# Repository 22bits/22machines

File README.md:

# 22machines

  Sistema modular electromecánico de generación y activación sonora, derivado de Tutupá drum machine, y desarrollado en Chile por el [Colectivo 22bits](https://www.22bits.org) (Bárbara Molina y Matías Serrano). 
  
  Motivados por un pensamiento tecnofeminista, proponemos replantearnos la tecnología y su incidencia en los cuerpos. Esta plataforma busca promover el bricolaje electrónico en comunidades latinoamericanas, y se propone como una alternativa, desde nuestros materiales y componentes disponibles en esta parte del mundo, al formato Eurorack. Todos los módulos se comunican a través de pulsos de 5v, y son alimentados por fuentes DC de 9 a 12v. Si no entiendes de qué estamos hablando, ve al apartado de preguntas frecuentes al final de la página.
  
  Únete a nuestra comunidad de experimentación en [Facebook!](https://www.facebook.com/groups/442825269573096/) 

  ### [C01-SEQ](https://github.com/22bits/22machines/tree/master/C01-SEQ)

    Secuenciador de 4 pistas y 16 pasos

  ### [C02-BEAT](https://github.com/22bits/22machines/tree/master/C02-BEAT)

    Conversor de trigger a movimiento percusivo de servomotor para 4 pistas

  ### [C03-MULT](https://github.com/22bits/22machines/tree/master/C03-MULT)

    Multiplicador pasivo, permite copiar una señal en otras dos. Cada módulo incluye 4 mults

  ### [C04-LD12](https://github.com/22bits/22machines/tree/master/C04-LD)

    Convierte un pulso en una señal de 12V, de longitud variable. Permite utilizar cargas de 12V, como tiras LED.

  ### [C05-22mini](https://github.com/22bits/22machines/tree/master/C05-22mini) 

    Drum machine mecánica, controladora de servos de 2 pasos y 8 pistas.
    Utilizada en talleres de introducción al sistema 22machines.

_________________________

 ### [¿? Preguntas frecuentes](https://github.com/22bits/22machines/tree/master/FAQ)
 
 ____________________
<br /><span xmlns:dct="http://purl.org/dc/terms/" href="http://purl.org/dc/dcmitype/InteractiveResource" property="dct:title" rel="dct:type">22machines</span> por <a xmlns:cc="http://creativecommons.org/ns#" href="http://www.22bits.org" property="cc:attributionName" rel="cc:attributionURL">Bárbara Molina & Matías Serrano</a> se distribuye bajo una <a rel="license" href="http://creativecommons.org/licenses/by-nc-sa/4.0/">Licencia Creative Commons Atribución-NoComercial-CompartirIgual 4.0 Internacional</a>.

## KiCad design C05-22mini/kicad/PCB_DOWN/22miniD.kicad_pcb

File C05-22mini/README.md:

# C05-22mini
(tutumini)

##### Diseñada por Colectivo 22bits (http://22bits.org)
##### Bárbara Molina & Matías Serrano
##### Programada por Elías Zacarías (http://blog.damnsoft.org/)
___________________________________

22mini es una drum machine mecánica de 2 pistas y 8 pasos, donde cada relación entra paso y pista puede activar un servo motor en una acción percusiva.

(click en la imagen para ver video)

### Especificaciones (1a versión):

    - 2 pistas con salidas individuales
    - Hasta 8 pasos por pista
    - Salidas pueden ser para controlar servo motores o generar triggers de 5v
    - Control de tempo
    - Control de Play/Pause/Clear
    - 2 pantallas de visualización, 
    - Entrada y salida de Sync no dependientes 
    - Cada máquina puede seleccionar si obedece al pulso externo o al interno a través de un switch
    - Operación a través de 9~12V con centro positivo
    
### Descripción de funcionamiento
  
22mini está programada en Arduino, la cual lee la información ingresada a través de los botones, lo muestra en la pantalla de LEDS, y activa los servomotores según la secuencia. La velocidad de ésta es dependiente de la perilla de tempo o de la entrada de Sync, que avanza un paso a cada lectura de pulso en Sync IN.

Electrónicamente, todos los componentes están en función del Arduino. 8 de los 9 botones ingresan a través de un circuito integrado CD4021 (PISO; Parallel IN, Serial OUT), el cuál permite leer 8 entradas paralelas utilizando solo tres pines del Arduino. El noveno botón ingresa directamente a éste. Los botones de la columna izquiera permiten seleccionar qué pista quiero escribir, y los de la fila inferior en qué paso quiero activar la secuencia. El botón de OFFBEAT permite visualizar entre pasos impares (1, 3, 5 y 7) y pares (2, 4, 6, 8). MUTE, al mantenerse presionado, permite silenciar una pista o pasos, dejando la oportunidad de generar patrones de 1/8 hasta 8/8. El botón de Play permite pausar o reproducir la secuencia, y al mantenerse presionado limpia todas las secuencias.
    
Las luces LED son controladas a través de un circuito integrado MAX4219, el cuál está diseñado para manejar matrices LED de hasta 8x8. Está sobreestimado, ya que solo maneja 17 leds de 64 posibles. La razón será explicada más adelante, en la sección de modificaciones. 

El tempo es controlado por pulsos de 5v y 15ms. Cada vez que Arduino recibe uno de estos pulsos, entiende que debe avanzar un paso la secuencia. Este pulso puede provenir internamente, obedeciendo al potenciómetro de TEMPO, o de forma externa, obedeciendo a la entrada SYNC IN. Este permite sincronizar 22minis entre ellas, o con otros secuenciadores (como los Korg, por ejemplo). Cada 22mini copia en la salida Sync OUT el tempo al cuál está avanzando. El Switch SYNC EXT/INT permite que la secuencia avance según el tempo externo o interno a disposición, evitando que cada 22mini sea esclava de la entrada de sync, y pueda independizase de esta, generando nuevos ritmos complejos.

Las salidas están predeterminadas para controlar servomotores en un movimiento percusivo. Practicamente cualquier servomotor de 5v y 180º es posible de activar, siempre y cuando no supere 1A de consumo. Cada salida de servo es alimentada por un único regulador 7805, por lo que la limitación de amperaje depende de éste. 

La alimentación del circuito puede ser de 9 a 12V, con un amperaje de 1A para motores más pequeños (como el SG09)
    
### Modificaciones sugeridas
    
   - 22mini está programada exactamente con el mismo código que C01-SEQ, solo varía a través de la línea "#define _22_MINI". Si está comentada, asignará los botones y leds para la versión de 4 pistas y 16 pasos, lo cual puede generar problemas para una 22mini.
   
   - Si se comenta la línea "#define SERVO_OUTPUT", las salidas pasan a ser de triggers de 5V, lo que permitiría utilizar estas para activar otro tipo de actuadores, usarlos como sync para otros secuenciadores, etc. Además cada conector cuenta con 5v (hasta 1A) y un GND.
   
   - La pantalla puede ser re-programada para que cuente hasta 16 pasos, y así tener más posibilidades rítmicas. Se sugiere utilizar dos horizontales para este conteo. Esta modificación no ha sido programada aún.
   
   - Hay pads de la PCB que no incluyen componentes, los cuales están abiertos para agregar variaciones. Estos son 4 pines análogos (A4, A5, A6, A7), uno digital (D3), D10 y D11 para salidas no definidas en el código, TX y RX.  

### Sugerencias al ensamblar:
  
   - D23 y R19 reducen el voltaje de la entrada de SYNC, no deben soldarse.
   - El emisor de Q1 debe ir a GND, por lo que se debe puentear al disipador.
   - Los Condensadores electrolíticos deben ir horizontales para que no interfieran espacialmente con la placa superior. Pueden ir soldados hacia arriba o hacia abajo según criterio de la persona que lo ensamble.
   - Soldar los headers utilizando los separadores como guías, para hacer más sencillo el montaje y desmontaje de las dos placas

 _____________________________
 
C05 - 22mini por Bárbara Molina & Matías Serrano se distribuye bajo una Licencia Creative Commons Atribución-NoComercial-CompartirIgual 4.0 Internacional.
 
Colectivo 22bits promueve cualquier tipo de modificación y hackeo a la máquina, no así el uso comercial que se le pueda dar sin expresa autorización de sus creadores. Si te fabricas una, la utilizas en tu set, o la usas para algo nuevo, haznos saber y te compartiremos en nuestras redes sociales (si te interesa) :)

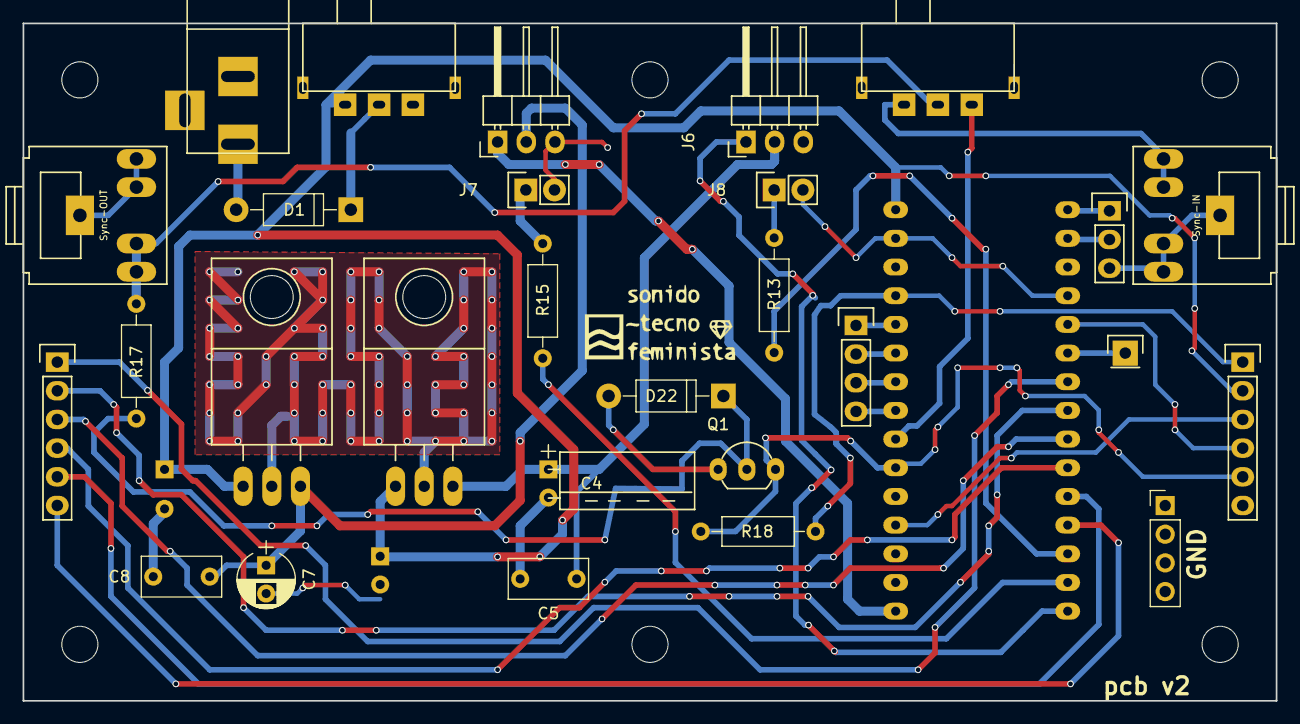
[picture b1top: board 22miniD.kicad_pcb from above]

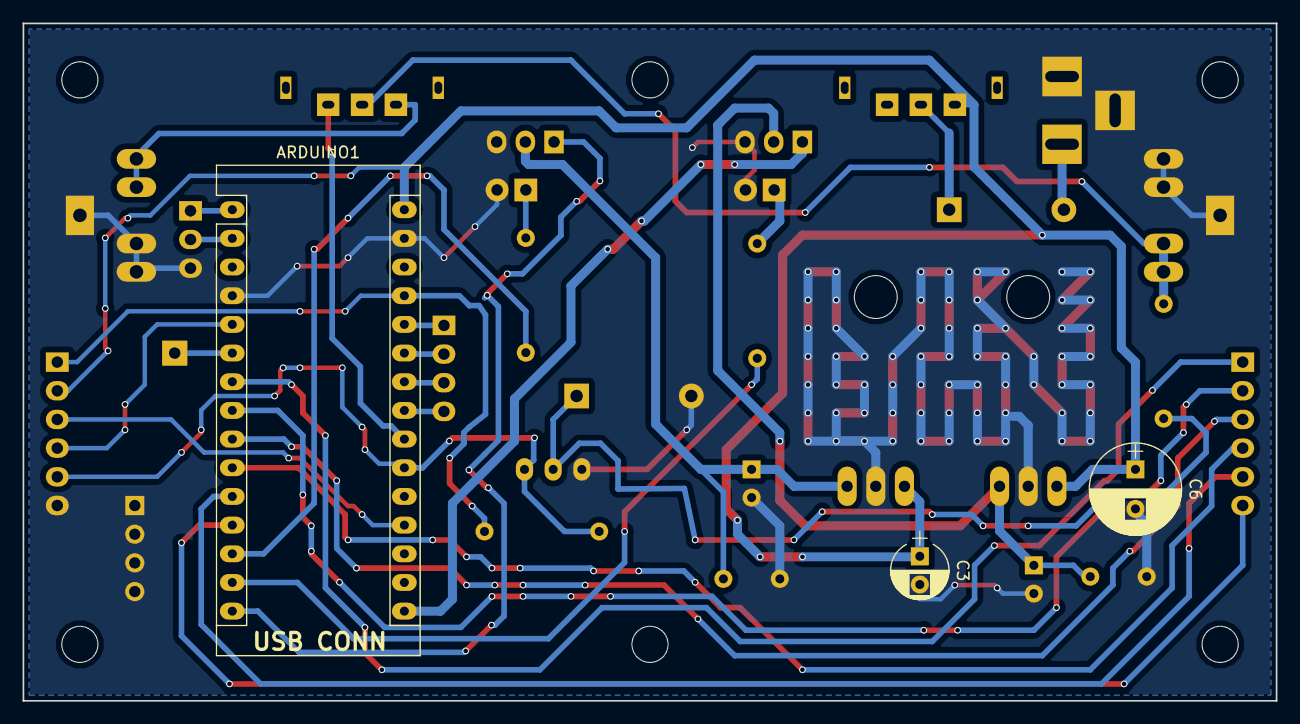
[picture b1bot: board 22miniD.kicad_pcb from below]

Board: 2 copper layers, 111.0 x 60.0 mm, 30 parts (3 on the bottom side), 33 nets.

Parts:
ARDUINO1: ARDUINO_NANO; Arduino_Nano
C3: 100u; CP_Radial_D5.0mm_P2.50mm
C4, C7: 10u; CP_Radial_D5.0mm_P2.50mm
C5, C8: 100n; C_Rect_L7.0mm_W3.5mm_P5.00mm
C6: 100u; CP_Radial_D8.0mm_P3.50mm
D1, D22: 1N4007; D_DO-41_SOD81_P10.16mm_Horizontal
J1: DC_IN; BARREL_JACK
J2: D3; Pin_Header_Straight_1x01
J3: TXRX; Pin_Header_Straight_1x03
J4: ANALOGS; Pin_Header_Straight_1x04
J5: SERVO1; Pin_Header_Angled_1x03
J6: SERVO2; Pin_Header_Angled_1x03
J7: OUT1; Pin_Header_Straight_1x02
J8: OUT2; Pin_Header_Straight_1x02
J9: Sync-IN; Tayda_3.5mm_stereo_TRS_jack_A-853
J10: Sync-OUT; Tayda_3.5mm_stereo_TRS_jack_A-853
J11: 4021/7219DOWN; Socket_Strip_Straight_1x06
J14: AUX BUS DOWN; Socket_Strip_Straight_1x06
Q1: PN2222A; TO-92_Inline_Wide
R13, R15: 100R; R_Axial_DIN0207_L6.3mm_D2.5mm_P10.16mm_Horizontal
R17: 1K; R_Axial_DIN0207_L6.3mm_D2.5mm_P10.16mm_Horizontal
R18: 10k; R_Axial_DIN0207_L6.3mm_D2.5mm_P10.16mm_Horizontal
SW4: ON/OFF; SW_SPDT_Lateral
SW11: SYNCSEL; SW_SPDT_Lateral
U3, U4: L7805; TO-220_Neutral123_Horizontal_LargePads

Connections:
+5V: ARDUINO1.27, J14.1, R18.2
+5VL: C4.1, C5.1, J6.2, U3.3
+5VP: C7.1, C8.1, J5.2, U4.3
+12V: ARDUINO1.30, C3.1, C6.1, J14.2, SW4.1, U3.1, U4.1
GND: ARDUINO1.4, ARDUINO1.29, C3.2, C4.2, C5.2, C6.2, C7.2, C8.2, D22.2, J1.2, J1.3, J3.3, J5.3, J6.3, J7.2, J8.2, J9.1, J9.2, J9.4, J10.1, J10.2, J10.4, J14.6, Q1.1, U3.2, U4.2
unnamed: ARDUINO1.1, J3.1
unnamed: ARDUINO1.2, J3.2
unnamed: ARDUINO1.5, J14.4
unnamed: ARDUINO1.6, J2.1
unnamed: ARDUINO1.7, J11.1
unnamed: ARDUINO1.8, J11.2
unnamed: ARDUINO1.9, J11.3
unnamed: ARDUINO1.10, J11.4
unnamed: ARDUINO1.11, J11.5
unnamed: ARDUINO1.12, J11.6
unnamed: ARDUINO1.13, R13.2
unnamed: ARDUINO1.14, R15.2
unnamed: ARDUINO1.15, J6.1
unnamed: ARDUINO1.16, J5.1
unnamed: ARDUINO1.19, J14.3
unnamed: ARDUINO1.21, J14.5, Q1.3, R18.1
unnamed: ARDUINO1.22, SW11.3
unnamed: ARDUINO1.23, J4.4
unnamed: ARDUINO1.24, J4.3
unnamed: ARDUINO1.25, J4.2
unnamed: ARDUINO1.26, J4.1
unnamed: D1.1, SW4.2
unnamed: D1.2, J1.1
unnamed: D22.1, Q1.2, R17.1
unnamed: J7.1, R15.1
unnamed: J8.1, R13.1
unnamed: J9.3, J9.5, SW11.1
unnamed: J10.3, J10.5, R17.2, SW11.2

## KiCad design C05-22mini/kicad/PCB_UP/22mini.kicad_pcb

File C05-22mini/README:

C05 - 22mini
(tutumini)
Diseñada por Colectivo 22bits (http://22bits.org)
Bárbara Molina & Matías Serrano
Programada por Elías Zacarías (http://blog.damnsoft.org/)

C05 - 22mini por Bárbara Molina & Matías Serrano se distribuye bajo una Licencia Creative Commons Atribución-NoComercial-CompartirIgual 4.0 Internacional.
___________________________________

22mini es una drum machine mecánica de 2 pistas y 8 pasos, donde cada relación entra paso y pista puede activar un servo motor en una acción percusiva.

  Especificaciones (1a versión):

    - 2 pistas con salidas individuales
    - Hasta 8 pasos por pista
    - Salidas pueden ser para controlar servo motores o generar triggers de 5v
    - Control de tempo
    - Control de Play/Pause/Clear
    - 2 pantallas de visualización, 
    - Entrada y salida de Sync no dependientes 
    - Cada máquina puede seleccionar si obedece al pulso externo o al interno a través de un switch
    - Operación a través de 9~12V con centro positivo
    
  Descripción de funcionamiento
  
    22mini está programada en Arduino, la cual lee la información ingresada a través de los botones, lo muestra en la pantalla de LEDS, y activa los servomotores según la secuencia. La velocidad de ésta es dependiente de la perilla de tempo o de la entrada de Sync, que avanza un paso a cada lectura de pulso en Sync IN.
    Electrónicamente, todos los componentes están en función del Arduino. 8 de los 9 botones ingresan a través de un circuito integrado CD4021 (PISO; Parallel IN, Serial OUT), el cuál permite leer 8 entradas paralelas utilizando solo tres pines del Arduino. El noveno botón ingresa directamente a éste. Los botones de la columna izquiera permiten seleccionar qué pista quiero escribir, y los de la fila inferior en qué paso quiero activar la secuencia. El botón de OFFBEAT permite visualizar entre pasos impares (1, 3, 5 y 7) y pares (2, 4, 6, 8). MUTE, al mantenerse presionado, permite silenciar una pista o pasos, dejando la oportunidad de generar patrones de 1/8 hasta 8/8. El botón de Play permite pausar o reproducir la secuencia, y al mantenerse presionado limpia todas las secuencias.
    Las luces LED son controladas a través de un circuito integrado MAX4219, el cuál está diseñado para manejar matrices LED de hasta 8x8. Está sobreestimado, ya que solo maneja 17 leds de 64 posibles. La razón será explicada más adelante, en la sección de modificaciones. 
    El tempo es controlado por pulsos de 5v y 15ms. Cada vez que Arduino recibe uno de estos pulsos, entiende que debe avanzar un paso la secuencia. Este pulso puede provenir internamente, obedeciendo al potenciómetro de TEMPO, o de forma externa, obedeciendo a la entrada SYNC IN. Este permite sincronizar 22minis entre ellas, o con otros secuenciadores (como los Korg, por ejemplo). Cada 22mini copia en la salida Sync OUT el tempo al cuál está avanzando. El Switch SYNC EXT/INT permite que la secuencia avance según el tempo externo o interno a disposición, evitando que cada 22mini sea esclava de la entrada de sync, y pueda independizase de esta, generando nuevos ritmos complejos.
    Las salidas están predeterminadas para controlar servomotores en un movimiento percusivo. Practicamente cualquier servomotor de 5v y 180º es posible de activar, siempre y cuando no supere 1A de consumo. Cada salida de servo es alimentada por un único regulador 7805, por lo que la limitación de amperaje depende de éste. 
    La alimentación del circuito puede ser de 9 a 12V, con un amperaje de 1A para motores más pequeños (como el SG09)
    
 Modificaciones
    
    - 22mini está programada exactamente con el mismo código que C01-SEQ, solo varía a través de la línea "#define _22_MINI". Si está comentada, asignará los botones y leds para la versión de 4 pistas y 16 pasos, lo cual puede generar problemas para una 22mini.
    - Si se comenta la línea "#define SERVO_OUTPUT", las salidas pasan a ser de triggers de 5V, lo que permitiría utilizar estas para activar otro tipo de actuadores, usarlos como sync para otros secuenciadores, etc. Además cada conector cuenta con 5v (hasta 1A) y un GND.
    - La pantalla puede ser re-programada para que cuente hasta 16 pasos, y así tener más posibilidades rítmicas. Se sugiere utilizar dos horizontales para este conteo. Esta modificación no ha sido programada aún.
    - Hay pads de la PCB que no incluyen componentes, los cuales están abiertos para agregar variaciones. Estos son 4 pines análogos (A4, A5, A6, A7), uno digital (D3), D10 y D11 para salidas no definidas en el código, TX y RX.  

  Sugerencias al ensamblar:
  
    - D23 y R19 reducen el voltaje de la entrada de SYNC, no deben soldarse.
    - El emisor de Q1 debe ir a GND, por lo que se debe puentear al disipador.
    - Los Condensadores electrolíticos deben ir horizontales para que no interfieran espacialmente con la placa superior. Pueden ir soldados hacia arriba o hacia abajo según criterio de la persona que lo ensamble.
    - Soldar los headers utilizando los separadores como guías, para hacer más sencillo el montaje y desmontaje de las dos placas

 _____________________________

Colectivo 22bits promueve cualquier tipo de modificación y hackeo a la máquina, no así el uso comercial que se le pueda dar sin expresa autorización de sus creadores. Si te fabricas una, la utilizas en tu set, o la usas para algo nuevo, haznos saber y te compartiremos en nuestras redes sociales (si te interesA) :)

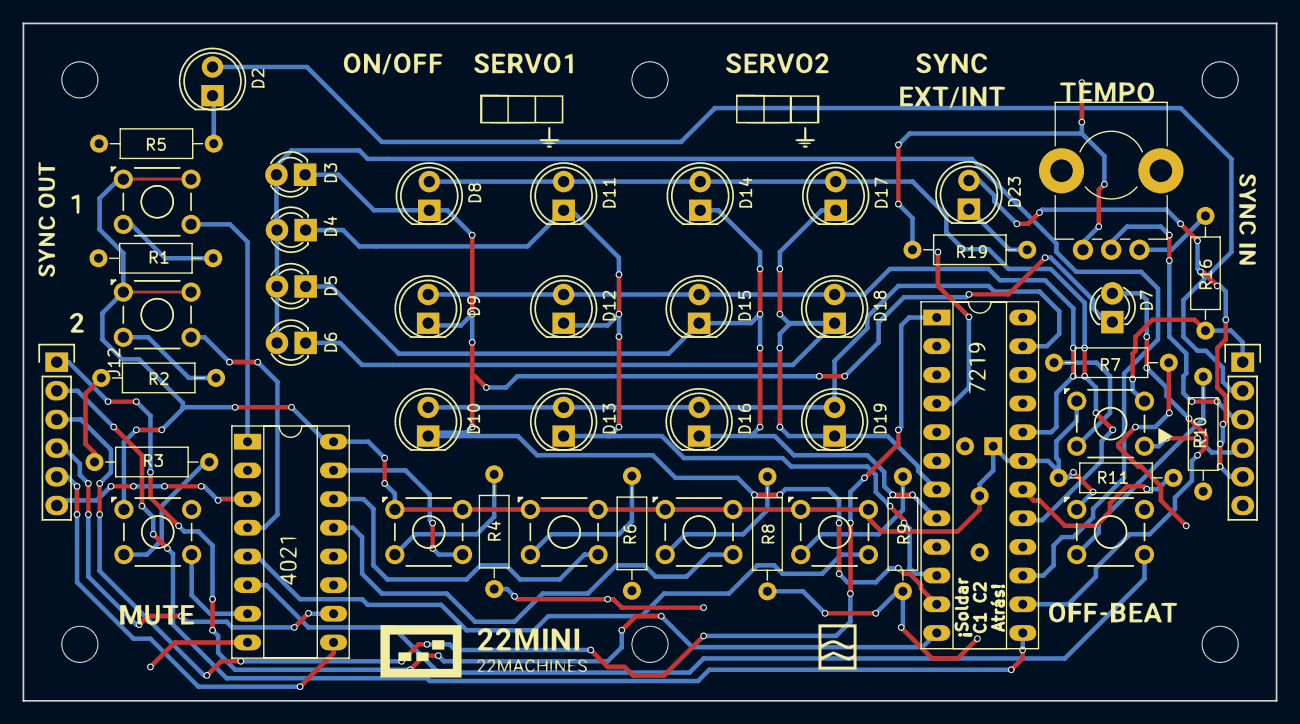
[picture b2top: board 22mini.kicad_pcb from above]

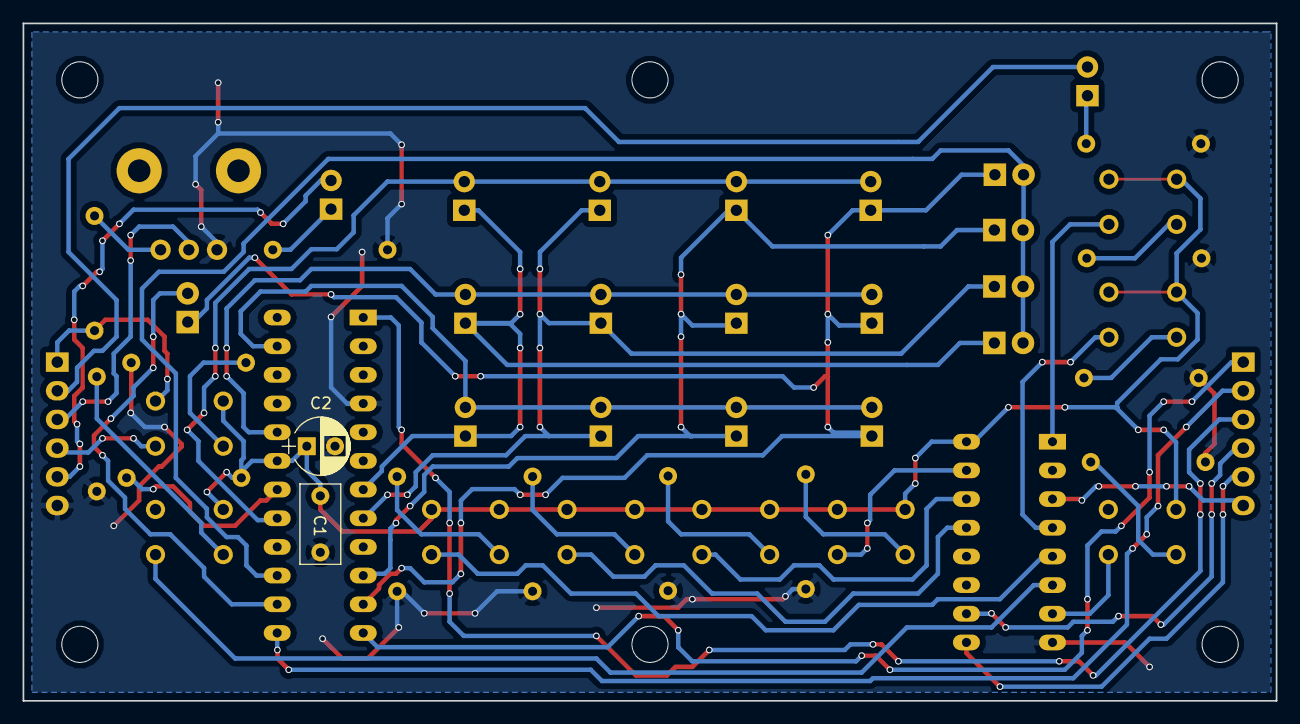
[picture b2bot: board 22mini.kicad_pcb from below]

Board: 2 copper layers, 111.0 x 60.0 mm, 48 parts (2 on the bottom side), 42 nets.

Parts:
C1: 100n; C_Rect_L7.0mm_W3.5mm_P5.00mm
C2: 10u; CP_Radial_D5.0mm_P2.50mm
D2: LEDONOFF; LED-5MM
D3: T1W; LED-3MM
D4: T1R; LED-3MM
D5: T2W; LED-3MM
D6: T2R; LED-3MM
D7: OFFBEAT_LED; LED-3MM
D8: T1P0; LED-5MM
D9: T2P0; LED-5MM
D10: CK0; LED-5MM
D11: T1P1; LED-5MM
D12: T2P1; LED-5MM
D13: CK1; LED-5MM
D14: T1P2; LED-5MM
D15: T2P2; LED-5MM
D16: CK2; LED-5MM
D17: T1P3; LED-5MM
D18: T2P3; LED-5MM
D19: CK3; LED-5MM
D23: TEMPOLED; LED-5MM
J12: 4021/7219UP; Socket_Strip_Straight_1x06
J13: AUX BUS UP; Socket_Strip_Straight_1x06
R1, R2, R3, R4, R6, R8, R9, R11: 10K; R_Axial_DIN0207_L6.3mm_D2.5mm_P10.16mm_Horizontal
R5: 1K; R_Axial_DIN0207_L6.3mm_D2.5mm_P10.16mm_Horizontal
R7, R10: R; R_Axial_DIN0207_L6.3mm_D2.5mm_P10.16mm_Horizontal
R16, R19: 220R; R_Axial_DIN0207_L6.3mm_D2.5mm_P10.16mm_Horizontal
RV1: TEMPO; Potentiometer_Alps_RK09K_Horizontal
SW1: TR01; SW_TH_Tactile_Omron_B3F-10xx
SW2: TR02; SW_TH_Tactile_Omron_B3F-10xx
SW3: MUTE; SW_TH_Tactile_Omron_B3F-10xx
SW5: ST01; SW_TH_Tactile_Omron_B3F-10xx
SW6: ST02; SW_TH_Tactile_Omron_B3F-10xx
SW7: PLAY/PAUSE/CLEAR; SW_TH_Tactile_Omron_B3F-10xx
SW8: ST03; SW_TH_Tactile_Omron_B3F-10xx
SW9: ST04; SW_TH_Tactile_Omron_B3F-10xx
SW10: OFFBEAT; SW_TH_Tactile_Omron_B3F-10xx
U1: 4021; DIP-16_W7.62mm_Socket_LongPads
U2: MAX7219; DIP-24_W7.62mm_Socket_LongPads

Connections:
+5V: C1.1, C2.1, J13.1, R11.1, R16.2, SW1.1, SW1.2, SW2.1, SW2.2, SW3.1, SW3.2, SW5.1, SW5.2, SW6.1, SW6.2, SW7.1, SW7.2, SW8.1, SW8.2, SW9.1, SW9.2, SW10.1, SW10.2, U1.16, U2.19
+12V: D2.2, J13.2
GND: C1.2, C2.2, J13.6, R1.1, R2.1, R3.1, R4.1, R5.1, R6.1, R7.1, R8.1, R9.1, R10.1, R19.1, RV1.3, U1.8, U2.4
unnamed: J13.4, SW7.4
unnamed: J12.1, U2.12
unnamed: J12.2, U2.13
unnamed: J12.3, U2.1
unnamed: J12.4, U1.10
unnamed: J12.5, U1.9
unnamed: J12.6, U1.3
unnamed: J13.3, RV1.2
unnamed: D23.2, J13.5
unnamed: D2.1, R5.2
unnamed: D3.2, D4.2, D5.2, D6.2, U2.15
unnamed: D7.2, U2.14
unnamed: D3.1, D7.1, D8.1, D9.1, D10.1, U2.11
unnamed: D10.2, D13.2, D16.2, D19.2, U2.23
unnamed: D4.1, D11.1, D12.1, D13.1, U2.10
unnamed: D8.2, D11.2, D14.2, D17.2, U2.17
unnamed: D9.2, D12.2, D15.2, D18.2, U2.20
unnamed: D5.1, D14.1, D15.1, D16.1, U2.8
unnamed: D6.1, D17.1, D18.1, D19.1, U2.7
unnamed: D23.1, R19.2
unnamed: R1.2, SW1.3
unnamed: R2.2, SW2.3
unnamed: R3.2, SW3.3
unnamed: R4.2, SW5.3
unnamed: R6.2, SW6.3
unnamed: R7.2, SW7.3
unnamed: R8.2, SW8.3
unnamed: R9.2, SW9.3
unnamed: R10.2, SW10.3
unnamed: R11.2, U2.18
unnamed: R16.1, RV1.1
unnamed: SW1.4, U1.1
unnamed: SW2.4, U1.4
unnamed: SW3.4, U1.7
unnamed: SW5.4, U1.15
unnamed: SW6.4, U1.14
unnamed: SW8.4, U1.13
unnamed: SW9.4, U1.5
unnamed: SW10.4, U1.6

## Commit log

2018-09-05 Create LICENSE
2018-09-05 Added 22mini code
2018-09-05 Creado el LEEME
2018-09-05 Actualizado código
2018-09-05 Subido esquemático
2018-09-05 Subido BOM
2018-09-05 Rename LEEME to LEEME.txt
2018-09-05 Rename LEEME.txt to README
2018-09-06 Agregado mapa de componentes
2018-10-15 Agregados nuevos módulos
    Agregados C01, C02, C03, C04
2018-10-15 agregadoesquematico c03
2018-10-15 Rename README.md to README
2018-10-15 edición de diagramación
    asd
2018-10-15 editado esquematico22mini
2018-10-16 Update FAQ/README
2018-10-17 Subidos kicad 22mini
2018-10-17 actualizado pcb down
2018-10-23 Rename README to README.md
2018-10-23 Create images
2018-10-23 crear images, gerbrs 22mini
2018-12-05 Actualizado BOM
2019-02-11 Revisado esquemático
2019-04-16 Añadido archivo de modificaciones
2020-04-10 actualizado esquemático
    Agregados diodos flyback, condensadores a la entrada de 555
2020-04-10 cambio nombre
    cam
